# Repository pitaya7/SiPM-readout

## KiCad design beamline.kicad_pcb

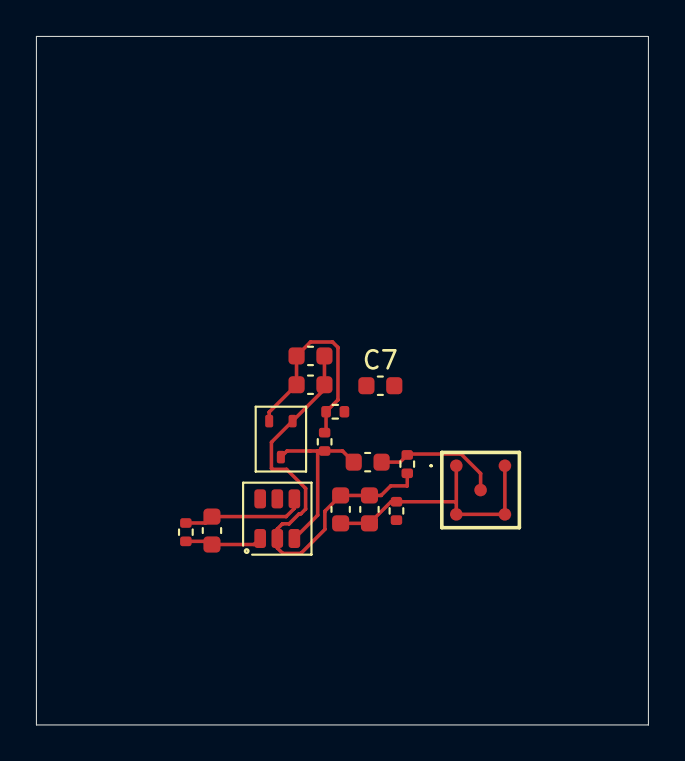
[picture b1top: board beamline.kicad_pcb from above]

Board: 2 copper layers, 34.0 x 38.2 mm, 16 parts (1 on the bottom side), 7 nets.

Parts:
C1: 100n; C_0603_1608Metric
C2: 10n; C_0603_1608Metric
C3, C5: 1u; C_0603_1608Metric
C4: Capacitor_NP; C_0603_1608Metric
C6: 0.1u; C_0603_1608Metric
C7: 10p; C_0603_1608Metric
D1: AFBR-S4N44P014M; AFBRS4N44P014M
D2: BAT64-04W; SOT-323_SC-70
J1: Conn_02x10_Socket; 2x10_P2.54mm_Socket_Vertical_SMD
R1: 10; R_0402_1005Metric
R2: 1k; R_0402_1005Metric
R3: Resistor; R_0402_1005Metric
R4, R5: 2k; R_0402_1005Metric
U1: OPAMP_5-pin_Generic; SOT-23-6

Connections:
/Bias Voltage/HV: C1.2, C2.2, C7.2, R1.2
/SiPM signal: C3.1, R2.2
GND: C1.1, C2.1, C5.1, C6.1, C7.1, D2.1 (A), R2.1, U1.2 (V-)
unnamed: C4.2, R3.2, U1.1
unnamed: C3.2, D2.3 (C), R4.1, U1.3 (+)
unnamed: C5.2, C6.2, D2.2 (K), R4.2, R5.2
unnamed: C4.1, R3.1, U1.4 (-)

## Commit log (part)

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2026-06-15 started
2026-06-15 6/15
2026-06-19 daq-poll.ino v0.1
2026-06-25 test
2026-06-28 adding stuff
